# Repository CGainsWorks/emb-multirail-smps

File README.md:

# emb-multirail-smps

> **Status: designed and validated in simulation, captured in KiCad. No
> hardware exists.** The electrical design is complete: specification,
> topology, sizing, hand derived loop compensation and a cycle accurate
> switching simulation that confirms the compensation gives the margins it was
> designed for. Real parts are selected, the schematic is captured in KiCad and
> held to the simulation by CI and a four layer board is laid out with five
> connections still unrouted and no layout review yet. **No board has been
> fabricated, assembled, powered or measured.** Everything under
> `test-results/` is computed. See [STATUS.md](STATUS.md) for the precise
> breakdown.

A four rail switch-mode supply for an 8 to 36 V DC input: a synchronous buck, a
second buck cascaded from it, a synchronous boost and a low noise LDO. 21.4 W
delivered at the connectors.

---

## The result this repository exists for

A schematic is a drawing. What makes a supply design worth reading is evidence
that the loop compensation derived on paper actually produces the crossover and
phase margin it claims. So this repository derives each loop by hand, then
measures the same loop off a switching simulation of the converter using the
same injection method a Bode analyser uses, and compares.

| rail | control | target fc | hand derived | simulated | error | target PM | hand derived | simulated | error |
|---|---|---|---|---|---|---|---|---|---|
| +5V | peak current mode | 50 kHz | 50.5 kHz | 50.8 kHz | +0.5 % | 55 deg | 60.9 deg | 62.8 deg | +1.9 deg |
| +3V3 | voltage mode | 100 kHz | 100.2 kHz | 99.1 kHz | -1.2 % | 55 deg | 63.3 deg | 65.9 deg | +2.6 deg |
| +12V | peak current mode | 6 kHz | 5.94 kHz | 6.26 kHz | +5.5 % | 50 deg | 76.6 deg | 78.3 deg | +1.7 deg |

Worst crossover disagreement 5.5 percent, worst phase margin disagreement 2.6
degrees. The brief this project was built to says not to order boards until the
simulation matches the hand calculation. It does.

The two traces are produced by code that shares nothing but the component
values. The hand derived line comes from state space averaging with the current
loop closed analytically; the points come from running the switching converter
cycle by cycle and measuring. They separate above about a fifth of the
switching frequency, which is exactly where an averaged model is supposed to
stop being accurate.

### A third opinion, from a tool that knows nothing about this repository

The hand derivation and the switching simulator are both mine, which is a
weakness: a shared misconception would agree with itself. So the compensator
networks are also emitted as **ngspice** decks and run on every push, with the
results compared against the closed forms.

ngspice is free, open source and the simulator inside KiCad. Each compensator
deck is passive components plus one ideal controlled source, so ngspice and
`smps.compensation` are solving the same linear system by completely different
means and have to agree to numerical precision. They do:

| deck | worst gain error | worst phase error |
|---|---|---|
| +5V Type II | 0.0000 dB | 0.000 deg |
| +12V Type II | 0.0000 dB | 0.000 deg |
| +3V3 Type III | 0.0001 dB | 0.099 deg |
| input filter | 0.0000 dB | magnitude only |

The enforced tolerance is 0.01 dB and 0.2 degrees, set just above what is
achieved rather than at a comfortable round number, so it is a guarantee rather
than somewhere for drift to hide. The 0.099 degrees is the whole of the
disagreement and it is explained: the deck's amplifier has a gain of a million
and the closed form it is compared against has an infinite one.

The switching deck is also run. ngspice settles the +3V3 rail at **3.3210 V**
against the 3.3210 V the feedback divider asks for, and reads 4.23 mVpp of
ripple against 2.74 mVpp from the simulator here. That factor of 1.54 is close
to the 1.6 the check allows, and it grew from 1.41 when the TPS54317's 0.891 V
reference replaced the assumed 0.8 V. The two are compared against
each other rather than only against the 20 mVpp limit, because both can sit
under a limit while disagreeing by a factor of two, and that disagreement is
the interesting number.

LTspice decks are emitted too, in a separate directory, and **have never been
run**: it is a Windows and Mac GUI with no Linux package, so no runner can
execute it. The two dialects are genuinely not interchangeable, which an
earlier version of this repository wrongly claimed; `Rser=`, `IF()` and
`LIMIT()` are LTspice extensions that ngspice rejects, and a test now asserts
none of them reaches an ngspice deck.

### The schematic is the circuit that was simulated

The brief named Altium; the schematic and board are in KiCad 8 instead, in
[`hardware/kicad/`](hardware/kicad/). Every part has a real part number and
footprint: LTC3891, TPS54317, TPS43061 and LP5912-1.8 for the four rails,
with the inductors, shunts and capacitors the simulation was sized for. Each
controller's reference and error amplifier figures came from its data sheet
into the model and the compensation was re-derived with them; the tables
above are the result.

CI runs `kicad-cli` in a pinned KiCad image on every push:

| check | result |
|---|---|
| ERC, every severity | 0 errors, 0 warnings |
| exported netlist against the ngspice decks, the models, the compensation table and each rail's set point | 575 checks, 0 failures |
| DRC with schematic parity on the four layer board | 0 clearance, short or parity errors; 5 connections unrouted |

The cross-check is the point. Every R, L and C in every deck ngspice runs is
matched to the schematic part it stands for, by value after the DC bias
derating the model applies and by the nets it joins, so a value changed in
KiCad fails the build. The board is generated placement and autorouted copper
on the [`docs/stackup.md`](docs/stackup.md) stackup. It is DRC clean apart
from the five open connections listed in STATUS.md and has not been through
the review in [`docs/layout_rules.md`](docs/layout_rules.md), so it is a
starting point, not a board to order.

---

## Run it

```bash
pip install -r requirements.txt
make demo
```

About two minutes. It regenerates every plot, CSV and generated document in the
repository from the specification and the component values. Nothing under
`outputs/`, `test-results/`, `docs/spec.md` or `docs/validation_report.md` is
written by hand.

```bash
make test
```

129 tests, about a minute, no hardware needed. One of them skips unless
ngspice is installed; CI installs it. They include a set that reads the
generated CSVs back and fails if any number quoted in this README has drifted
away from them.

```bash
make check
```

Runs the tests, regenerates everything and fails if what is committed has
drifted from what the code produces. This is the check to run before
committing, and it is the check that matters most: a repository full of
committed CSVs that no longer match the code is worse than one with no CSVs at
all, because it looks authoritative.

### CI

One job, which does six things in order: runs the tests, regenerates every
output, checks the regenerated results still match what is committed, runs the
generated decks in **ngspice** and compares them against the Python models,
checks that every number this README quotes is still true and runs the
**KiCad** ERC, netlist cross-check and DRC. `make ci` runs the same sequence
locally; `make kicad` runs the KiCad part alone, with Docker.

It is built to be cheap, because the account that runs it is a free one:

| | |
|---|---|
| one job, not four | the checkout and the dependency install are paid for once and shared, rather than each check renting its own runner |
| path filters | a commit that only touches documentation does not start a runner at all |
| concurrency | pushing twice in a minute cancels the first run instead of paying for both |
| pip cache | the dependency install is the second largest cost after the simulation |
| `timeout-minutes` | a hung job cannot quietly consume a month's allowance |
| manual version matrix | 3.9 and 3.11 are checked on demand, not on every push, because what that catches is library behaviour and that does not change when this repository does. 3.12 runs on every push as the main job's interpreter |

Measured at about 2 minutes per push, against roughly 12 for the obvious
arrangement of one job per check.

**The outputs are compared as numbers, not as bytes.** A switching simulation
that finds its switching instants by iteration is not bit reproducible across
platforms: these settled voltages agree to about one part per million between
Windows with numpy 1.26 and Linux with numpy 2.5. That is three orders finer
than any claim made here, and insisting on bit equality would fail the build
for reasons that have nothing to do with the design. Every non-numeric token
still has to match exactly, so a renamed column, a reordered row or a changed
sentence is caught. `scripts/check_outputs_current.py` does the comparison and
always prints the worst deviation it saw, so drift is visible long before it
trips the threshold.

---

## The rails

| rail | topology | control | Vin | Vout | Iout | to connector | fsw |
|---|---|---|---|---|---|---|---|
| +5V | synchronous buck | peak current mode | 8 to 36 V | 5.0 V | 5.0 A | 1.5 A | 500 kHz |
| +3V3 | synchronous buck | voltage mode | +5V | 3.3 V | 3.0 A | 2.5 A | 1 MHz |
| +12V | synchronous boost | peak current mode | +5V | 12.0 V | 0.4 A | 0.4 A | 400 kHz |
| +1V8A | LDO | linear | +3V3 | 1.8 V | 0.5 A | 0.5 A | - |

The rails are cascaded rather than independent, so the +5V stage carries 4.6 A
when only 1.5 A of that reaches a connector. Working the tree backwards by hand
is where a power budget usually goes wrong, so it is done by code and asserted
in the tests. Full specification and the reasoning for the tree, the control
schemes and the switching frequencies: [`docs/spec.md`](docs/spec.md) and
[`docs/design_notes.md`](docs/design_notes.md).

---

## What is here

| | |
|---|---|
| [`docs/spec.md`](docs/spec.md) | The specification. Generated from `simulation/smps/spec.py`, which is the only place these numbers are written down |
| [`docs/design_notes.md`](docs/design_notes.md) | Why this power tree and these control schemes, sizing worked by hand, and the closed forms the numeric models are checked against |
| [`docs/compensation/`](docs/compensation/) | One file per loop, with the placement rules argued and the arithmetic written out |
| [`docs/validation_report.md`](docs/validation_report.md) | Generated. Every result in one place, with what was checked and what was not |
| [`docs/loss_model.md`](docs/loss_model.md) | Every loss term, and how wrong each one is likely to be |
| [`docs/thermal_model.md`](docs/thermal_model.md) | The two resistance model, and what it cannot say |
| [`docs/emc_prescan_method.md`](docs/emc_prescan_method.md) | The conducted emissions model, the limit line's status, and the input filter stability trade-off |
| [`docs/stackup.md`](docs/stackup.md) | Four layer stackup and fabrication notes |
| [`docs/layout_rules.md`](docs/layout_rules.md) | The constraints a layout has to satisfy for any of these results to mean anything |
| [`docs/bring_up.md`](docs/bring_up.md) | Bring-up procedure with a predicted value for every measurement. Not performed |
| [`hardware/kicad/`](hardware/kicad/) | KiCad 8 schematic and four layer board, with the custom symbols, net classes and design rules |
| [`outputs/`](outputs/) | Protel netlist for Altium, SPICE decks in both ngspice and LTspice dialects, BOM with part numbers, compensation values and the verification checklist |
| [`test-results/`](test-results/) | Simulated Bode, regulation, transient, efficiency, thermal and EMC results |
| [`simulation/smps/`](simulation/smps/) | The models. State space averaging, current mode loop closure, compensator design, the switching simulator and the virtual network analyser |

---

## How the loop measurement works

The interesting part of the simulator is not that it switches, it is how the
loop gain comes out of it.

A small sinusoid is injected in series with the feedback divider. The voltage
either side of the injection is recorded and the loop gain is `-VA/VB`, which
is the formula a Bode 100 uses. Three details make it clean:

**Commensurate frequencies.** Every sweep point is snapped to `fsw * k/M` and
exactly `M` switching cycles are recorded. The switching ripple is periodic at
`fsw`, so in a once-per-cycle sample sequence it lands entirely on the DC bin
and the transform at bin `k` rejects it *exactly*. No windowing, no averaging,
no leakage.

**A continuous stimulus.** The injection is generated by a two state oscillator
inside the simulated system rather than by a value held constant across each
switching cycle. A held value is a zero order hold, and it would add
`exp(-s Ts/2)` of phase lag to the answer that the real converter does not
have. On the +5V rail that artefact is 18 degrees at crossover, which is the
difference between a comfortable design and a marginal one. It was found by the
sim and the hand model disagreeing, and it was the sim that was wrong.

**A linearity check.** Every measurement is re-run at double amplitude; the
answer moves by around one part in ten thousand. That is the same check a
careful bench sweep does.

The measurement has the same limitation a real analyser triggered off the
switching clock has: sampling once per cycle puts a Nyquist limit at `fsw/2`,
so on two of the three rails the simulated sweep cannot reach the -180 degree
crossing and the gain margin is reported from the hand model only. That is
stated rather than papered over.

---

## Results

Every number below is produced by `make demo`. **All of them are simulated.**

### Regulation, ripple and transient

| rail | line regulation | load regulation | ripple | limit | load step | undershoot | limit |
|---|---|---|---|---|---|---|---|
| +5V | < 0.001 % over 8 to 36 V | 0.001 % | 6.4 mVpp | 25 mVpp | 1.5 A | 99 mV | 150 mV |
| +3V3 | < 0.001 % over the 5 V band | < 0.001 % | 2.7 mVpp | 20 mVpp | 1.0 A | 43 mV | 100 mV |
| +12V | 0.001 % over the 5 V band | 0.001 % | 25.7 mVpp | 50 mVpp | 0.2 A | 198 mV | 300 mV |

The regulation columns are quoted to three decimals of a percent and no further,
because that is where this solver stops meaning anything: it resolves a settled
output voltage to about one part per million, which is 0.0001 percent. Read them
as bounds, not as measurements of a converter that regulates to a part in
a hundred thousand.

The +5V line regulation looks too good, and there is a reason. With peak
current mode and the artificial ramp set equal to the falling inductor current
slope, the modulator gain goes as `1/Vin` while the control to output gain goes
as `Vin`, and the two cancel exactly in the averaged model. The test suite
asserts that cancellation to one part in a million, precisely so a reader who
suspects a bug can see it was checked. The real converter will not be perfectly
flat: dead time, gate driver timing and Rds(on) all move with operating point
and none of them are modelled.

### Efficiency

87.9 percent at 24 V and full load, input to useful output, including the cost
of the cascade. 24.4 W in, 21.4 W out, 2.95 W of loss.

At high line the +5V stage is dominated by switching loss, not conduction loss.
That is also the loss term with the widest error band, so if a bench
measurement ever disagrees with this curve, it is the first place to look.

### Thermal

3.3 W in still air, no heatsink, on a 100 by 80 mm four layer board. The high
side buck FET runs hottest at high line, 94.4 C junction against a 125 C limit,
and the LDO is second at 93.4 C. A linear regulator dropping 1.5 V at 0.5 A has
to put 0.68 W somewhere, and on a board with no heatsink that puts it in the
same league as the switching FET carrying the whole supply.

Maximum ambient for a 125 degree junction at full load is 85.7 degrees at high
line, against a 55 degree specification.

### Conducted emissions and input filter stability

Differential mode only, against the EN 55032 Class B line used as a reference
envelope. Worst margin **4.7 dB**, at the switching fundamental at low line.
That is thin, and it is called out as the weakest claim here.

The same input filter is also checked against Middlebrook's criterion, because
a converter in regulation is a constant power load and looks like a negative
resistance below its loop bandwidth. Worst separation 14.6 dB. This is why the
bulk capacitor is 220 uF rather than the 47 uF the ripple alone would ask for,
and the test suite asserts that shrinking it fails.

---

## Limitations

The full list is in [STATUS.md](STATUS.md). The ones that matter most:

* **Nothing has been measured.** No board, no parts, no instruments. Every
  directory called `test-results` contains simulation output.
* **The layout is not finished.** Five connections are unrouted and the
  generated placement and autorouted copper have not been reviewed against
  `docs/layout_rules.md`. KiCad, not Altium.
* **Parts are selected, not fully verified.** Every part is real and its
  headline figures were checked; `outputs/VERIFY.csv` lists where the data
  sheets and the model still disagree. The +3V3 regulator's FET resistance and
  the input filter parts are the ones that matter most.
* **Common mode emissions are not modelled**, because they depend on the
  parasitics of a finished, reviewed layout. On real hardware common mode is very often the term that
  actually fails.
* **The LDO loop model is behavioural.** That rail's compensation lives inside
  the LP5912 and the model was not refitted to it. What this design controls
  there is the output capacitor, the preload and the input filter.
* **Discontinuous conduction is not modelled**, so the light load end of every
  efficiency curve is optimistic.
* **The thermal model assumes an isothermal board**, which it will not be.

---

## Licence

MIT. See [LICENSE](LICENSE).

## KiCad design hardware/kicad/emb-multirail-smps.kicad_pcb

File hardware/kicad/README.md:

# KiCad project

KiCad 8 schematic and four layer board for the supply. KiCad is free and the
EDA tool a hardware team without an Altium licence would use; the brief named
Altium, which is not available here.

**Nothing here has been fabricated, assembled, powered or measured.**

| file | what it is |
|---|---|
| `emb-multirail-smps.kicad_sch` | Root sheet: the four stage sheets below and an overview |
| `input_5v.kicad_sch` | Input terminal, fuse, TVS, differential mode filter, +5V buck (LTC3891) |
| `buck_3v3.kicad_sch` | +3V3 voltage mode buck (TPS54317) and its Type III network |
| `boost_12v.kicad_sch` | +12V synchronous boost (TPS43061) |
| `ldo_outputs.kicad_sch` | +1V8A LDO (LP5912-1.8), its input RC filter, preload and the output terminal |
| `smps.kicad_sym` | Symbols for the two controllers KiCad's library does not ship, drawn from their data sheet pin tables |
| `emb-multirail-smps.kicad_pcb` | Four layer board, 100 by 80 mm, to `docs/stackup.md` |
| `emb-multirail-smps.kicad_pro` | Project, net classes and design rules |
| `emb-multirail-smps.kicad_dru` | One custom rule: pad to pad gaps inside library land patterns |

## Where the values come from

Every part carries a `Basis` field:

* `model`: the value the simulation in `simulation/smps` uses. The inductors,
  shunts, capacitor banks, dividers, compensation networks, the input filter
  and the LDO filter and preload.
* `datasheet`: support parts sized from the controller's data sheet, with
  the equation or table quoted in the part's description or note. Timing
  resistors, bootstrap, soft start, bias and bypass capacitors. These are not
  simulated.
* `choice`: a decision with no equation behind it, such as a pull-up value or
  a 0 ohm link.

Every part also has a real manufacturer part number in its `MPN` field. The
headline ratings of each were checked on the manufacturer's or a
distributor's listing; where the data sheet and the model disagree it is
written down in `outputs/VERIFY.csv`. Nothing has been ordered.

Each feedback divider has a 0603 0 ohm link between the rail and the top of
the divider (R14, R22, R32). Replacing it with 20 ohm gives the injection
point the bring-up Bode measurement needs.

## How it is checked

`scripts/kicad/run_checks.sh` does what CI does, in the pinned
`kicad/kicad:8.0.9` image:

1. `kicad-cli sch erc` with every severity enabled. It has to report nothing
   at all, warnings included.
2. `kicad-cli sch export netlist`, then `scripts/kicad/check_netlist.py`,
   which holds the exported netlist to the simulation: every R, L and C in
   every ngspice deck CI runs is matched to the part it stands for, by value
   (after the DC bias derating the model applies to ceramics) and by the nets
   it joins (after the 0 ohm links are closed); the inductors, shunts and
   capacitor banks are compared with `smps.components`; the compensation
   values with `outputs/compensation_values.csv`; and each regulated rail's
   set point is computed from the selected controller's reference and the
   divider. Change a value in KiCad and CI fails.
3. With `--board`, `kicad-cli pcb drc --schematic-parity`. Errors fail;
   warnings are listed.

## How it was made

The schematic was generated from `simulation/smps/hardware.py` by
`scripts/kicad/gen_schematic.py`, in the label style: every pin has a short
wire and a net label. That makes the connectivity explicit and checkable;
it is less pleasant to read than a schematic drawn by hand. Regenerate it with

    python scripts/kicad/gen_schematic.py --symbols <KiCad symbols directory>

and the check above confirms the result still matches.

The board was placed by `scripts/kicad/gen_pcb.py`, one region per stage with
the switching loop parts in the first row of each. It was routed by
`scripts/kicad/route_board.sh`: plane vias for every ground, VIN, +5V and +3V3
pad, 0.30 mm thermal vias under the exposed pads, Freerouting 2.4.1 for the
rest, power tracks widened afterwards as far as clearance allows and up to
three repair passes that take up whatever DRC objects to and route again.

**The board is not finished.** Five connections are unrouted (STATUS.md lists
them) and neither the generated placement nor the autorouted copper has been
through the review in `docs/layout_rules.md`. DRC is otherwise clean and CI
holds it there.

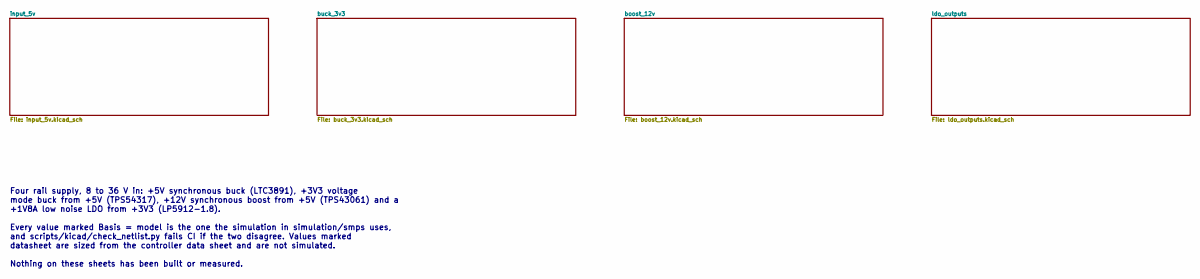
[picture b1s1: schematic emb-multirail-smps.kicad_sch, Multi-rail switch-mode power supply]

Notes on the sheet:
Four rail supply, 8 to 36 V in: +5V synchronous buck (LTC3891), +3V3 voltage mode buck from +5V (TPS54317), +12V synchronous boost from +5V (TPS43061) and a +1V8A low noise LDO from +3V3 (LP5912-1.8). Every value marked Basis = model is the one the simulation in simulation/smps uses, and scripts/ki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

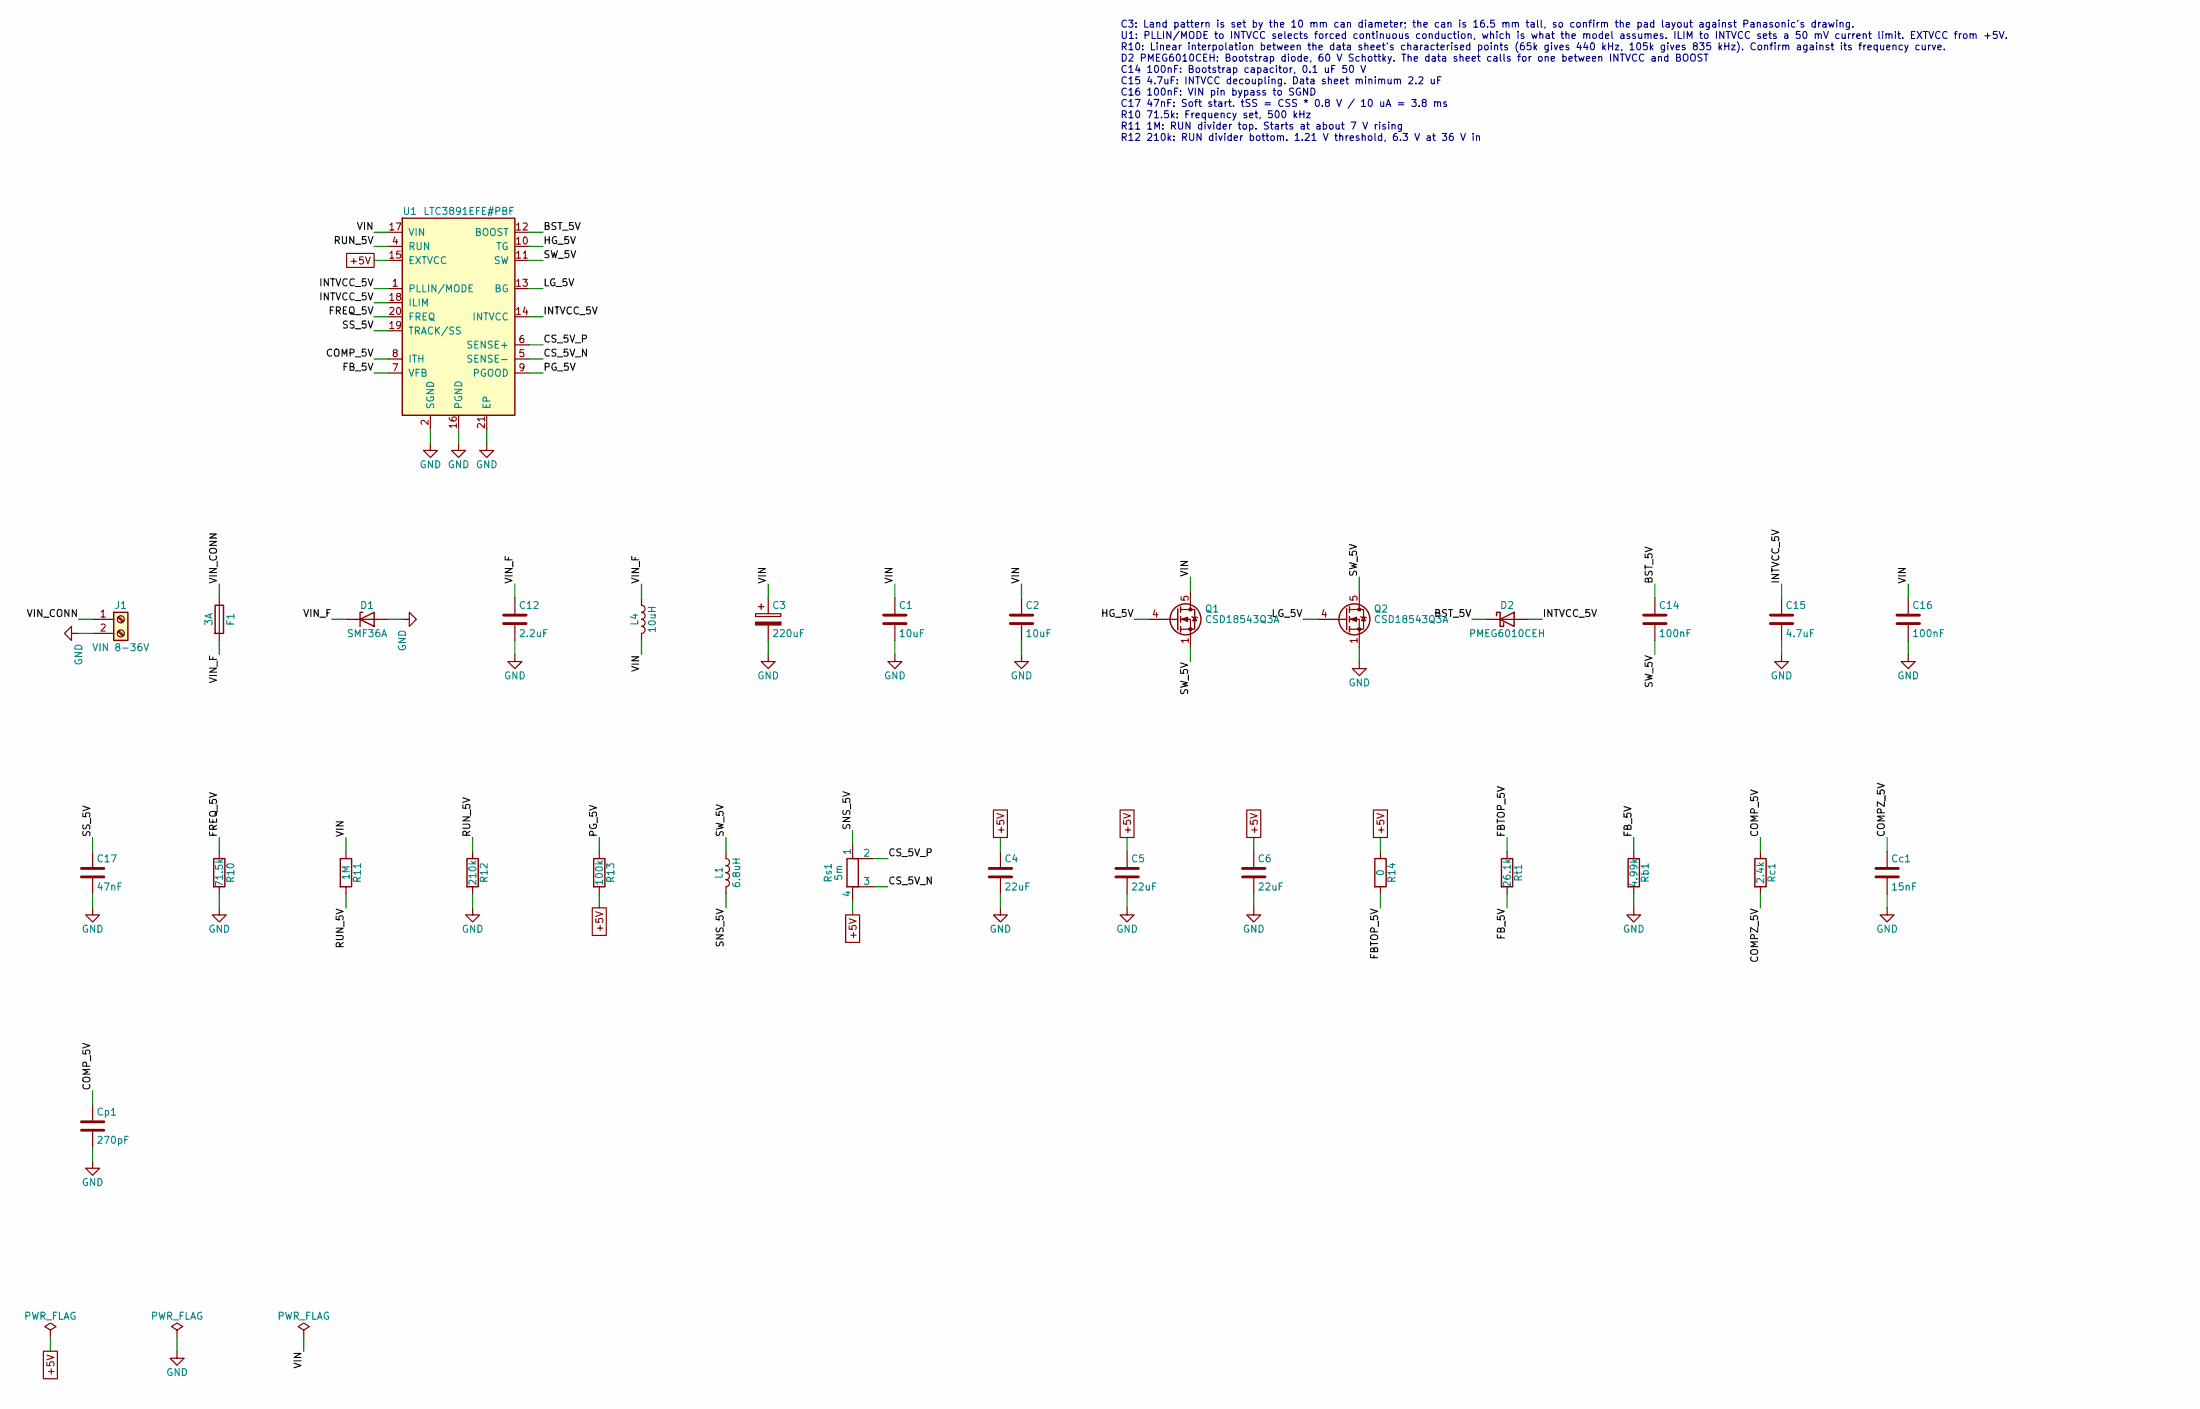
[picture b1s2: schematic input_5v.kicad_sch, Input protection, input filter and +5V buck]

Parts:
C1, C2: 10uF; C_1210_3225Metric; MPN GRM32ER71H106KA12L
C3: 220uF; CP_Elec_10x10.5; MPN EEH-ZS1H221P
C4, C5, C6: 22uF; C_1210_3225Metric; MPN GRM32ER71E226KE15L
C12: 2.2uF; C_1210_3225Metric; MPN GRM32ER72A225KA35L
C14: 100nF; C_0603_1608Metric; MPN GRM188R71H104KA93D
C15: 4.7uF; C_0805_2012Metric; MPN GRM21BR71C475KA73L
C16: 100nF; C_0402_1005Metric; MPN GRM155R71H104KE14D
C17: 47nF; C_0402_1005Metric; MPN GRM155R71C473KA01D
Cc1: 15nF; C_0402_1005Metric; MPN GRM155R71H153KA12D
Cp1: 270pF; C_0402_1005Metric; MPN C0402C271J5GACTU
D1: SMF36A; D_SOD-123F; MPN SMF36A
D2: PMEG6010CEH; D_SOD-123F; MPN PMEG6010CEH
F1: 3A; Fuse_1206_3216Metric; MPN CC12H3A-TR
J1: VIN 8-36V; TerminalBlock_Phoenix_MKDS-3-2-5.08_1x02_P5.08mm_Horizontal; MPN 1711725
L1: 6.8uH; L_Coilcraft_XAL8080-XXX; MPN XAL8080-682MED
L4: 10uH; L_Coilcraft_XAL7050-XXX; MPN XAL7050-103MEC
Q1, Q2: CSD18543Q3A; VSON-8_3.3x3.3mm_P0.65mm_NexFET; MPN CSD18543Q3A
R10: 71.5k; R_0402_1005Metric; MPN RC0402FR-0771K5L
R11: 1M; R_0603_1608Metric; MPN RC0603FR-071ML
R12: 210k; R_0402_1005Metric; MPN RC0402FR-07210KL
R13: 100k; R_0402_1005Metric; MPN RC0402FR-07100KL
R14: 0; R_0603_1608Metric; MPN RC0603JR-070RL
Rb1: 4.99k; R_0402_1005Metric; MPN RC0402FR-074K99L
Rc1: 2.4k; R_0402_1005Metric; MPN RC0402FR-072K4L
Rs1: 5m; R_Shunt_Vishay_WSK2512_6332Metric_T1.19mm; MPN WSK25125L000FEA
Rt1: 26.1k; R_0402_1005Metric; MPN RC0402FR-0726K1L
U1: LTC3891EFE#PBF; HTSSOP-20-1EP_4.4x6.5mm_P0.65mm_EP2.74x3.86mm; MPN LTC3891EFE#PBF

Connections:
+5V: C4.1, C5.1, C6.1, R13.2, R14.1, Rs1.4, U1.15 (EXTVCC); also elsewhere on the board
/input_5v/BST_5V: C14.1, D2.1 (K), U1.12 (BOOST)
/input_5v/COMPZ_5V: Cc1.1, Rc1.2
/input_5v/COMP_5V: Cp1.1, Rc1.1, U1.8 (ITH)
/input_5v/CS_5V_N: Rs1.3, U1.5 (SENSE-)
/input_5v/CS_5V_P: Rs1.2, U1.6 (SENSE+)
/input_5v/FBTOP_5V: R14.2, Rt1.1
/input_5v/FB_5V: Rb1.1, Rt1.2, U1.7 (VFB)
/input_5v/FREQ_5V: R10.1, U1.20 (FREQ)
/input_5v/HG_5V: Q1.4 (G), U1.10 (TG)
/input_5v/INTVCC_5V: C15.1, D2.2 (A), U1.1 (PLLIN/MODE), U1.14 (INTVCC), U1.18 (ILIM)
/input_5v/LG_5V: Q2.4 (G), U1.13 (BG)
/input_5v/PG_5V: R13.1, U1.9 (PGOOD)
/input_5v/RUN_5V: R11.2, R12.1, U1.4 (RUN)
/input_5v/SNS_5V: L1.2, Rs1.1
/input_5v/SS_5V: C17.1, U1.19 (TRACK/SS)
/input_5v/SW_5V: C14.2, L1.1, Q1.1 (S), Q1.2 (S), Q1.3 (S), Q2.5 (D), U1.11 (SW)
/input_5v/VIN: C1.1, C2.1, C3.1, C16.1, L4.2, Q1.5 (D), R11.1, U1.17 (VIN)
/input_5v/VIN_CONN: F1.1, J1.1
/input_5v/VIN_F: C12.1, D1.1 (K), F1.2, L4.1
GND: C1.2, C2.2, C3.2, C4.2, C5.2, C6.2, C12.2, C15.2, C16.2, C17.2, Cc1.2, Cp1.2, D1.2 (A), J1.2, Q2.1 (S), Q2.2 (S), Q2.3 (S), R10.2, R12.2, Rb1.2, U1.2 (SGND), U1.3 (SGND), U1.16 (PGND), U1.21 (EP); also elsewhere on the board

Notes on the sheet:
C3: Land pattern is set by the 10 mm can diameter; the can is 16.5 mm tall, so confirm the pad layout against Panasonic's drawing. U1: PLLIN/MODE to INTVCC selects forced continuous conduction, which is what the model assumes. ILIM to INTVCC sets a 50 mV current limit. EXTVCC from +5V. R10: Linear 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

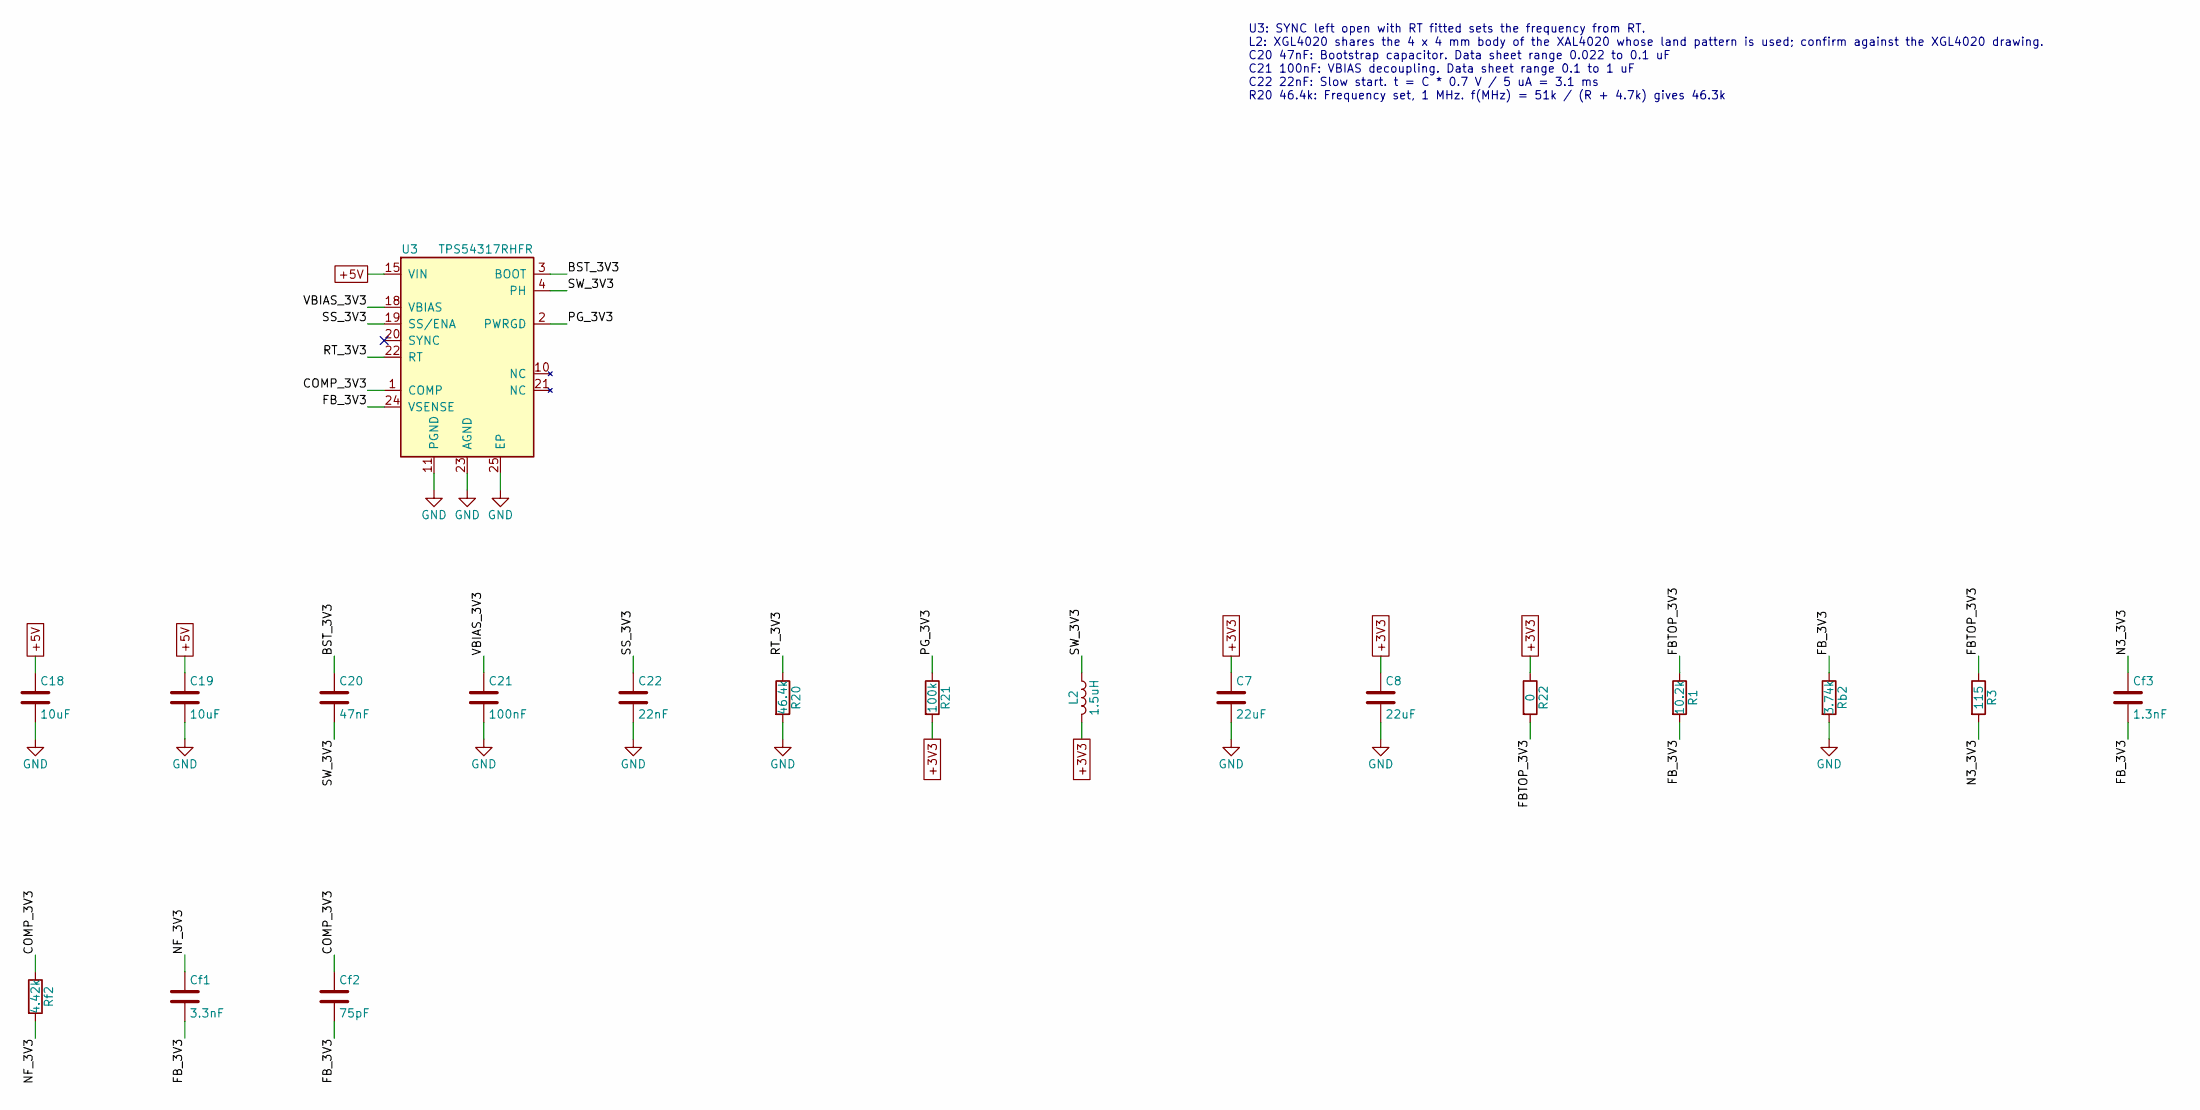
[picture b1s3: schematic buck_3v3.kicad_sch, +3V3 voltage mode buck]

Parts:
C7, C8: 22uF; C_1206_3216Metric; MPN GRM31CZ71C226ME15L
C18, C19: 10uF; C_0805_2012Metric; MPN CL21B106KOQNNNE
C20: 47nF; C_0402_1005Metric; MPN GRM155R71C473KA01D
C21: 100nF; C_0402_1005Metric; MPN GRM155R71H104KE14D
C22: 22nF; C_0402_1005Metric; MPN GRM155R71H223KA12D
Cf1: 3.3nF; C_0402_1005Metric; MPN GRM1555C1H332JE01D
Cf2: 75pF; C_0402_1005Metric; MPN C0402C750J5GACTU
Cf3: 1.3nF; C_0402_1005Metric; MPN C0402C132J5GACTU
L2: 1.5uH; L_Coilcraft_XAL4020-XXX; MPN XGL4020-152MEC
R1: 10.2k; R_0402_1005Metric; MPN RC0402FR-0710K2L
R3: 115; R_0402_1005Metric; MPN RC0402FR-07115RL
R20: 46.4k; R_0402_1005Metric; MPN RC0402FR-0746K4L
R21: 100k; R_0402_1005Metric; MPN RC0402FR-07100KL
R22: 0; R_0603_1608Metric; MPN RC0603JR-070RL
Rb2: 3.74k; R_0402_1005Metric; MPN RC0402FR-073K74L
Rf2: 4.42k; R_0402_1005Metric; MPN RC0402FR-074K42L
U3: TPS54317RHFR; QFN-24-1EP_4x5mm_P0.5mm_EP2.65x3.65mm; MPN TPS54317RHFR

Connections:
+3V3: C7.1, C8.1, L2.2, R21.2, R22.1; also elsewhere on the board
+5V: C18.1, C19.1, U3.15 (VIN), U3.16 (VIN), U3.17 (VIN); also elsewhere on the board
/buck_3v3/BST_3V3: C20.1, U3.3 (BOOT)
/buck_3v3/COMP_3V3: Cf2.1, Rf2.1, U3.1 (COMP)
/buck_3v3/FBTOP_3V3: R1.1, R3.1, R22.2
/buck_3v3/FB_3V3: Cf1.2, Cf2.2, Cf3.2, R1.2, Rb2.1, U3.24 (VSENSE)
/buck_3v3/N3_3V3: Cf3.1, R3.2
/buck_3v3/NF_3V3: Cf1.1, Rf2.2
/buck_3v3/PG_3V3: R21.1, U3.2 (PWRGD)
/buck_3v3/RT_3V3: R20.1, U3.22 (RT)
/buck_3v3/SS_3V3: C22.1, U3.19 (SS/ENA)
/buck_3v3/SW_3V3: C20.2, L2.1, U3.4 (PH), U3.5 (PH), U3.6 (PH), U3.7 (PH), U3.8 (PH), U3.9 (PH)
/buck_3v3/VBIAS_3V3: C21.1, U3.18 (VBIAS)
GND: C7.2, C8.2, C18.2, C19.2, C21.2, C22.2, R20.2, Rb2.2, U3.11 (PGND), U3.12 (PGND), U3.13 (PGND), U3.14 (PGND), U3.23 (AGND), U3.25 (EP); also elsewhere on the board

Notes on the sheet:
U3: SYNC left open with RT fitted sets the frequency from RT. L2: XGL4020 shares the 4 x 4 mm body of the XAL4020 whose land pattern is used; confirm against the XGL4020 drawing. C20 47nF: Bootstrap capacitor. Data sheet range 0.022 to 0.1 uF C21 100nF: VBIAS decoupling. Data sheet range 0.1 to 1 u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

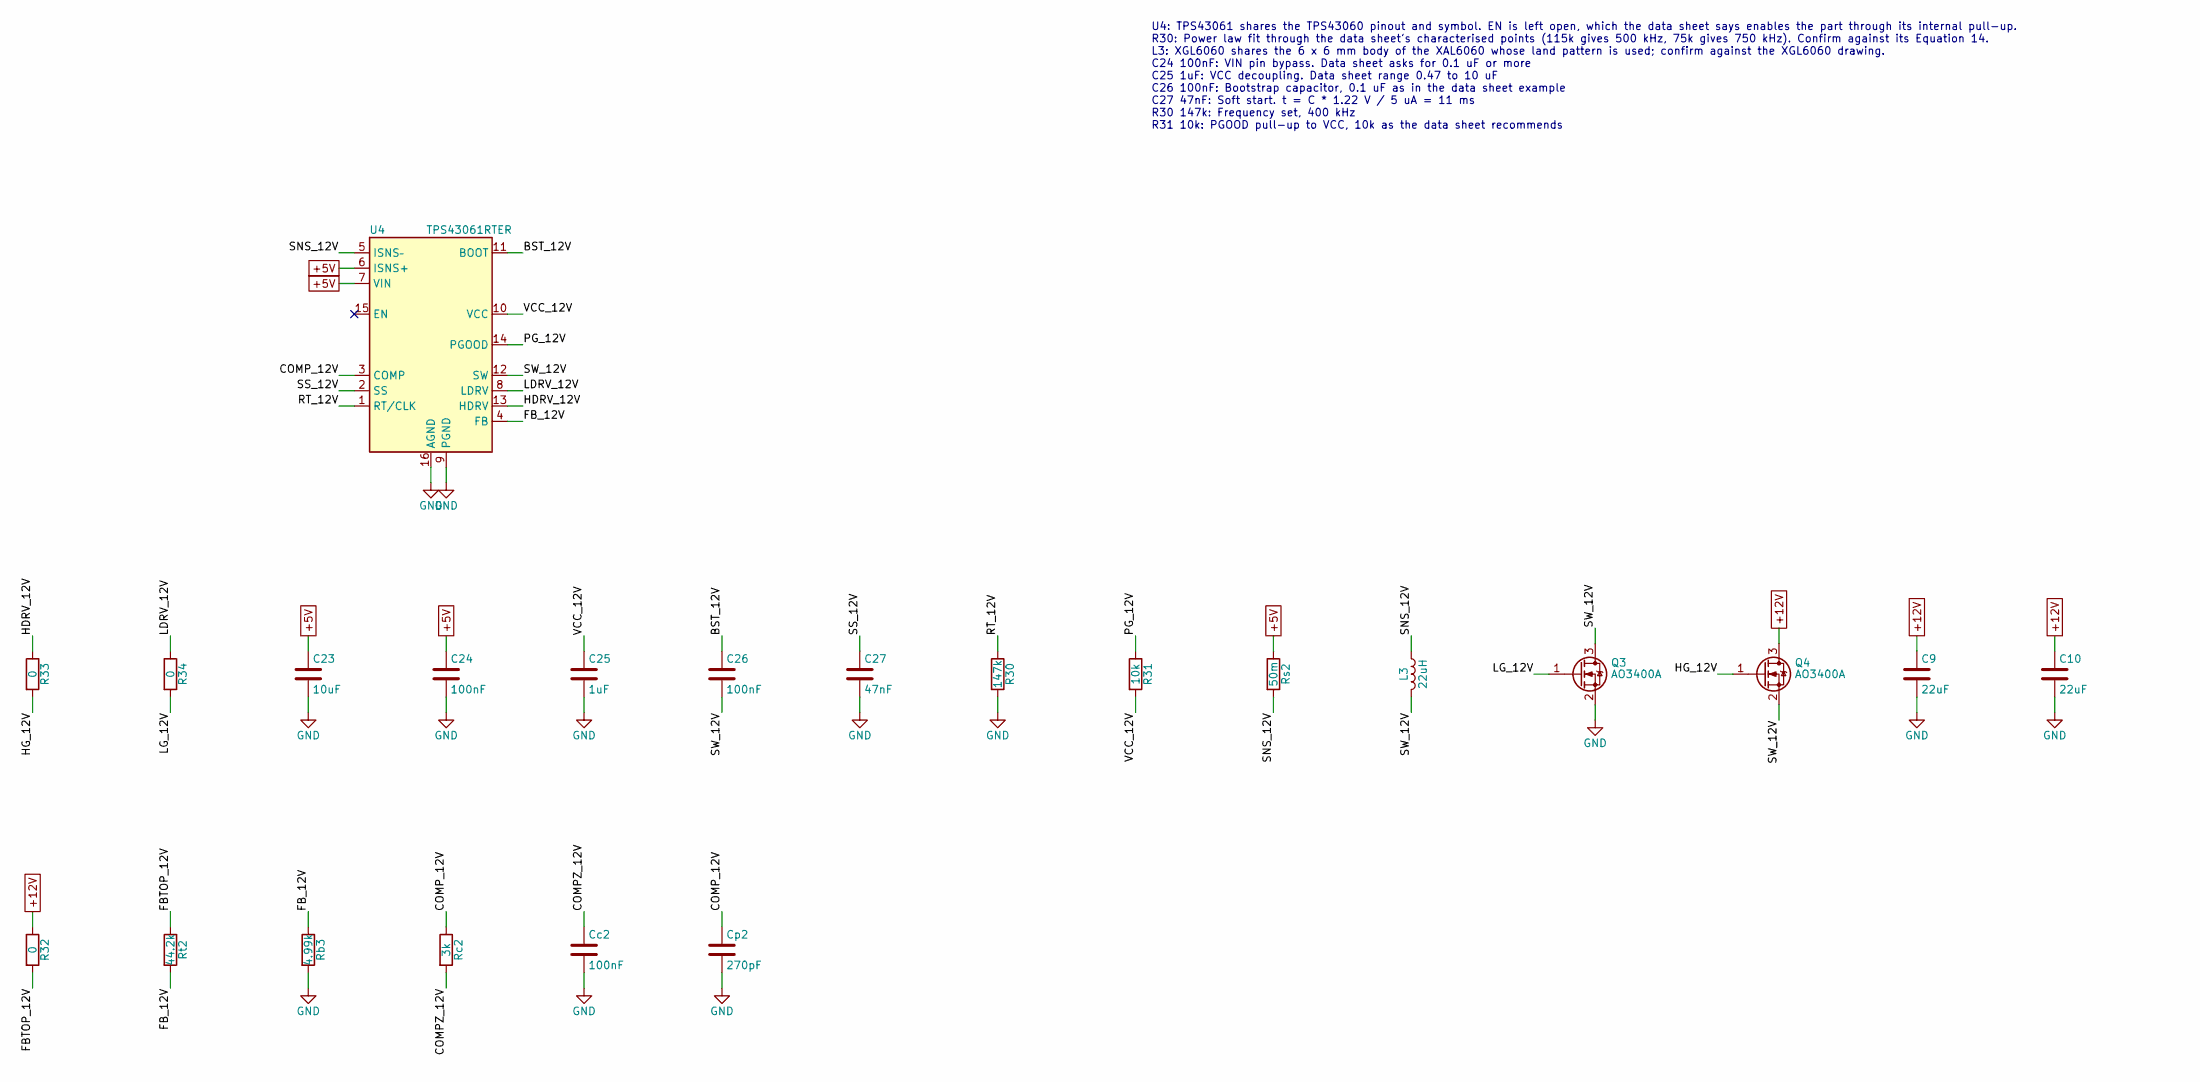
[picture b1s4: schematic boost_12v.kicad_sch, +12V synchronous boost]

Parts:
C9, C10: 22uF; C_1210_3225Metric; MPN GRM32ER71E226KE15L
C23: 10uF; C_0805_2012Metric; MPN CL21B106KOQNNNE
C24: 100nF; C_0402_1005Metric; MPN GRM155R71H104KE14D
C25: 1uF; C_0603_1608Metric; MPN GRM188R71C105KA12D
C26: 100nF; C_0603_1608Metric; MPN GRM188R71H104KA93D
C27: 47nF; C_0402_1005Metric; MPN GRM155R71C473KA01D
Cc2: 100nF; C_0402_1005Metric; MPN GRM155R71H104KE14D
Cp2: 270pF; C_0402_1005Metric; MPN C0402C271J5GACTU
L3: 22uH; L_Coilcraft_XAL6060-XXX; MPN XGL6060-223MEC
Q3, Q4: AO3400A; SOT-23; MPN AO3400A
R30: 147k; R_0402_1005Metric; MPN RC0402FR-07147KL
R31: 10k; R_0402_1005Metric; MPN RC0402FR-0710KL
R32: 0; R_0603_1608Metric; MPN RC0603JR-070RL
R33, R34: 0; R_0402_1005Metric; MPN RC0402JR-070RL
Rb3: 4.99k; R_0402_1005Metric; MPN RC0402FR-074K99L
Rc2: 3k; R_0402_1005Metric; MPN RC0402FR-073KL
Rs2: 50m; R_0805_2012Metric; MPN WSLP0805R0500FEA
Rt2: 44.2k; R_0402_1005Metric; MPN RC0402FR-0744K2L
U4: TPS43061RTER; Texas_RTE_WQFN-16-1EP_3x3mm_P0.5mm_EP1.2x0.8mm; MPN TPS43061RTER

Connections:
+5V: C23.1, C24.1, Rs2.1, U4.6 (ISNS+), U4.7 (VIN); also elsewhere on the board
+12V: C9.1, C10.1, Q4.3 (D), R32.1; also elsewhere on the board
/boost_12v/BST_12V: C26.1, U4.11 (BOOT)
/boost_12v/COMPZ_12V: Cc2.1, Rc2.2
/boost_12v/COMP_12V: Cp2.1, Rc2.1, U4.3 (COMP)
/boost_12v/FBTOP_12V: R32.2, Rt2.1
/boost_12v/FB_12V: Rb3.1, Rt2.2, U4.4 (FB)
/boost_12v/HDRV_12V: R33.1, U4.13 (HDRV)
/boost_12v/HG_12V: Q4.1 (G), R33.2
/boost_12v/LDRV_12V: R34.1, U4.8 (LDRV)
/boost_12v/LG_12V: Q3.1 (G), R34.2
/boost_12v/PG_12V: R31.1, U4.14 (PGOOD)
/boost_12v/RT_12V: R30.1, U4.1 (RT/CLK)
/boost_12v/SNS_12V: L3.1, Rs2.2, U4.5 (ISNS–)
/boost_12v/SS_12V: C27.1, U4.2 (SS)
/boost_12v/SW_12V: C26.2, L3.2, Q3.3 (D), Q4.2 (S), U4.12 (SW)
/boost_12v/VCC_12V: C25.1, R31.2, U4.10 (VCC)
GND: C9.2, C10.2, C23.2, C24.2, C25.2, C27.2, Cc2.2, Cp2.2, Q3.2 (S), R30.2, Rb3.2, U4.9 (PGND), U4.16 (AGND), U4.17 (AGND); also elsewhere on the board

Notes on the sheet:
U4: TPS43061 shares the TPS43060 pinout and symbol. EN is left open, which the data sheet says enables the part through its internal pull-up. R30: Power law fit through the data sheet's characterised points (115k gives 500 kHz, 75k gives 750 kHz). Confirm against its Equation 14. L3: XGL6060 shares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

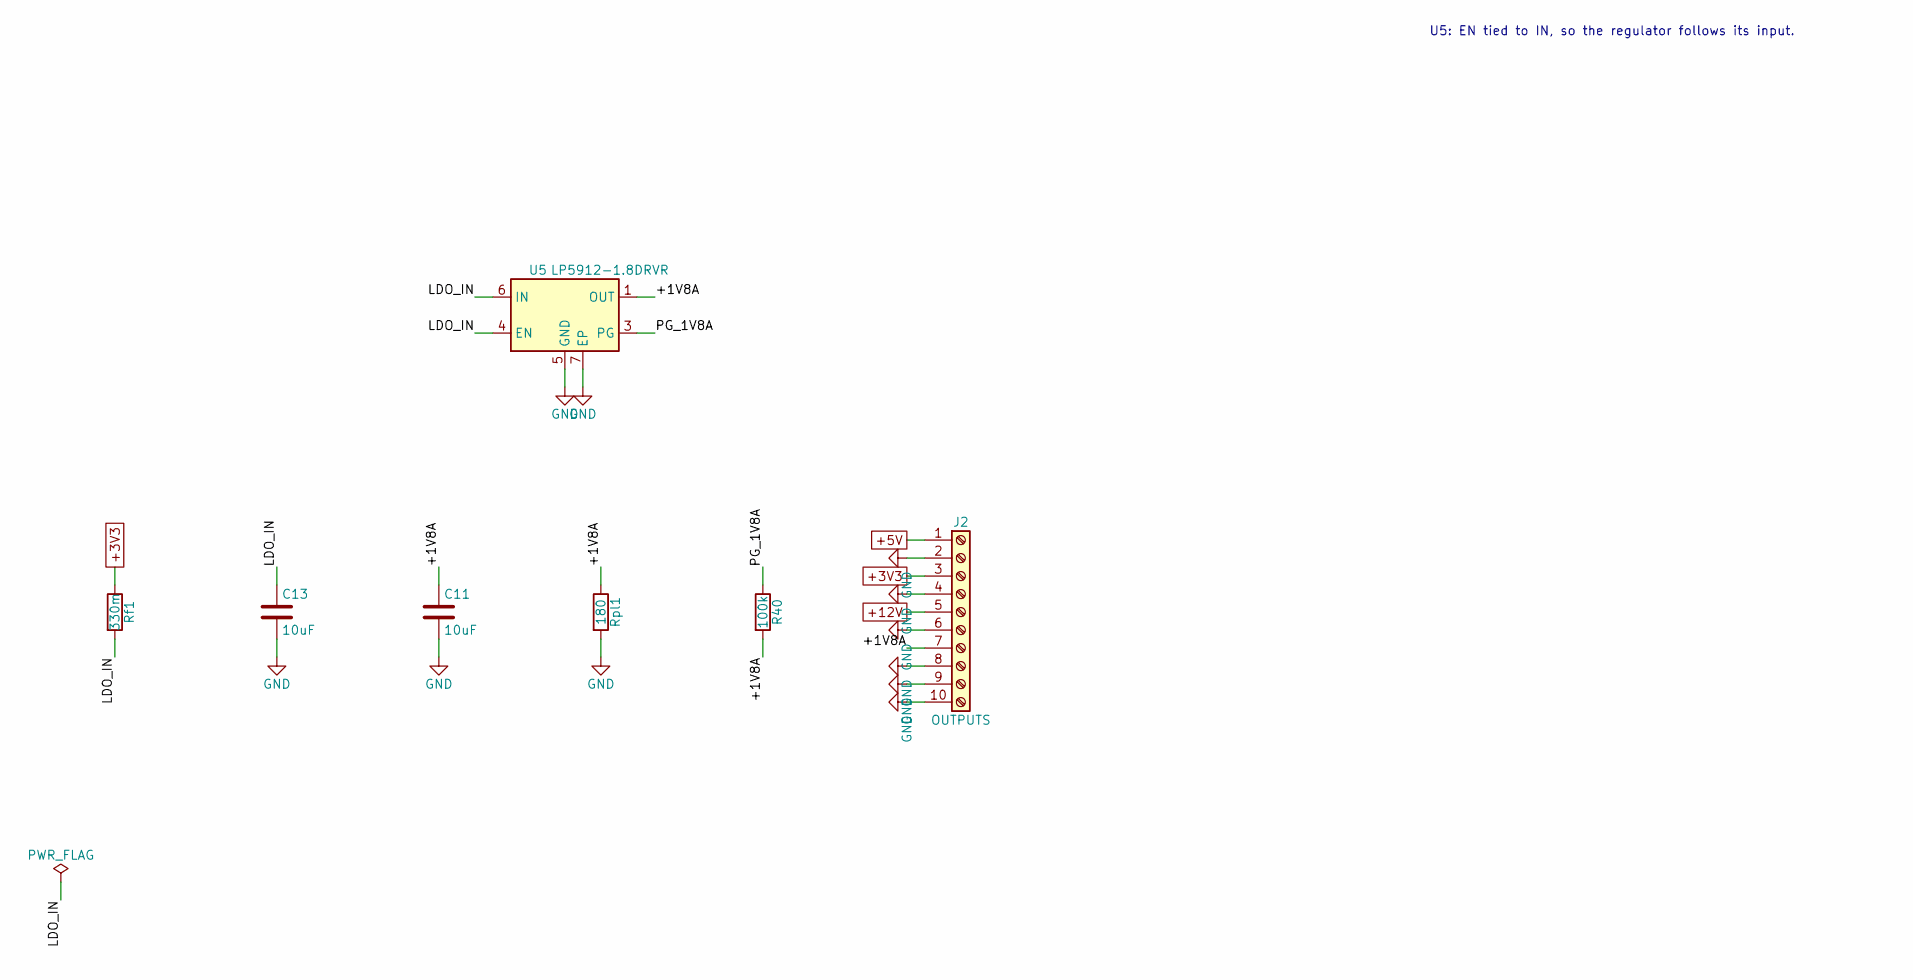
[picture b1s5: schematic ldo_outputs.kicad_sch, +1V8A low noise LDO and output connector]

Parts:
C11: 10uF; C_0805_2012Metric; MPN GRM21BR70J106KE76L
C13: 10uF; C_0805_2012Metric; MPN CL21B106KOQNNNE
J2: OUTPUTS; TerminalBlock_Phoenix_MKDS-1,5-10-5.08_1x10_P5.08mm_Horizon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; MPN 1715802
R40: 100k; R_0402_1005Metric; MPN RC0402FR-07100KL
Rf1: 330m; R_0805_2012Metric; MPN RL0805FR-7W0R33L
Rpl1: 180; R_0603_1608Metric; MPN RC0603FR-07180RL
U5: LP5912-1.8DRVR; WSON-6-1EP_2x2mm_P0.65mm_EP1x1.6mm; MPN LP5912-1.8DRVR

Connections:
+3V3: J2.3, Rf1.1; also elsewhere on the board
+5V: J2.1; also elsewhere on the board
+12V: J2.5; also elsewhere on the board
/ldo_outputs/+1V8A: C11.1, J2.7, R40.2, Rpl1.1, U5.1 (OUT)
/ldo_outputs/LDO_IN: C13.1, Rf1.2, U5.4 (EN), U5.6 (IN)
/ldo_outputs/PG_1V8A: R40.1, U5.3 (PG)
GND: C11.2, C13.2, J2.2, J2.4, J2.6, J2.8, J2.9, J2.10, Rpl1.2, U5.5 (GND), U5.7 (EP); also elsewhere on the board

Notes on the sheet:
U5: EN tied to IN, so the regulator follows its input.
